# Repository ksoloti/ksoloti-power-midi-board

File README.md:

# Ksoloti Power MIDI addon board

Kicad 6+

Libraries not included, you should be able to retrieve any custom symbols and footprints via the project itself.

3D models not included, always such a hassle with those files, can't be a%$ed.

Gerbers, BOM and CPL (placement) files for JLC included. You should be able to have the board with all SMD parts produced. The remaining (through-hole) parts required are all quite common: 2.54mm headers, DIN-5 MIDI jacks, DC barrel jack...

## Disclaimer: the files are provided as is. I guarantee nothing. Stay safe and double check. If you're not sure if you're doing it right, ask someone with more knowledge for help.

## Schematic
[ksoloti-power-midi-board.pdf](ksoloti-power-midi-board.pdf)

## Rear

## Front

## Bottom

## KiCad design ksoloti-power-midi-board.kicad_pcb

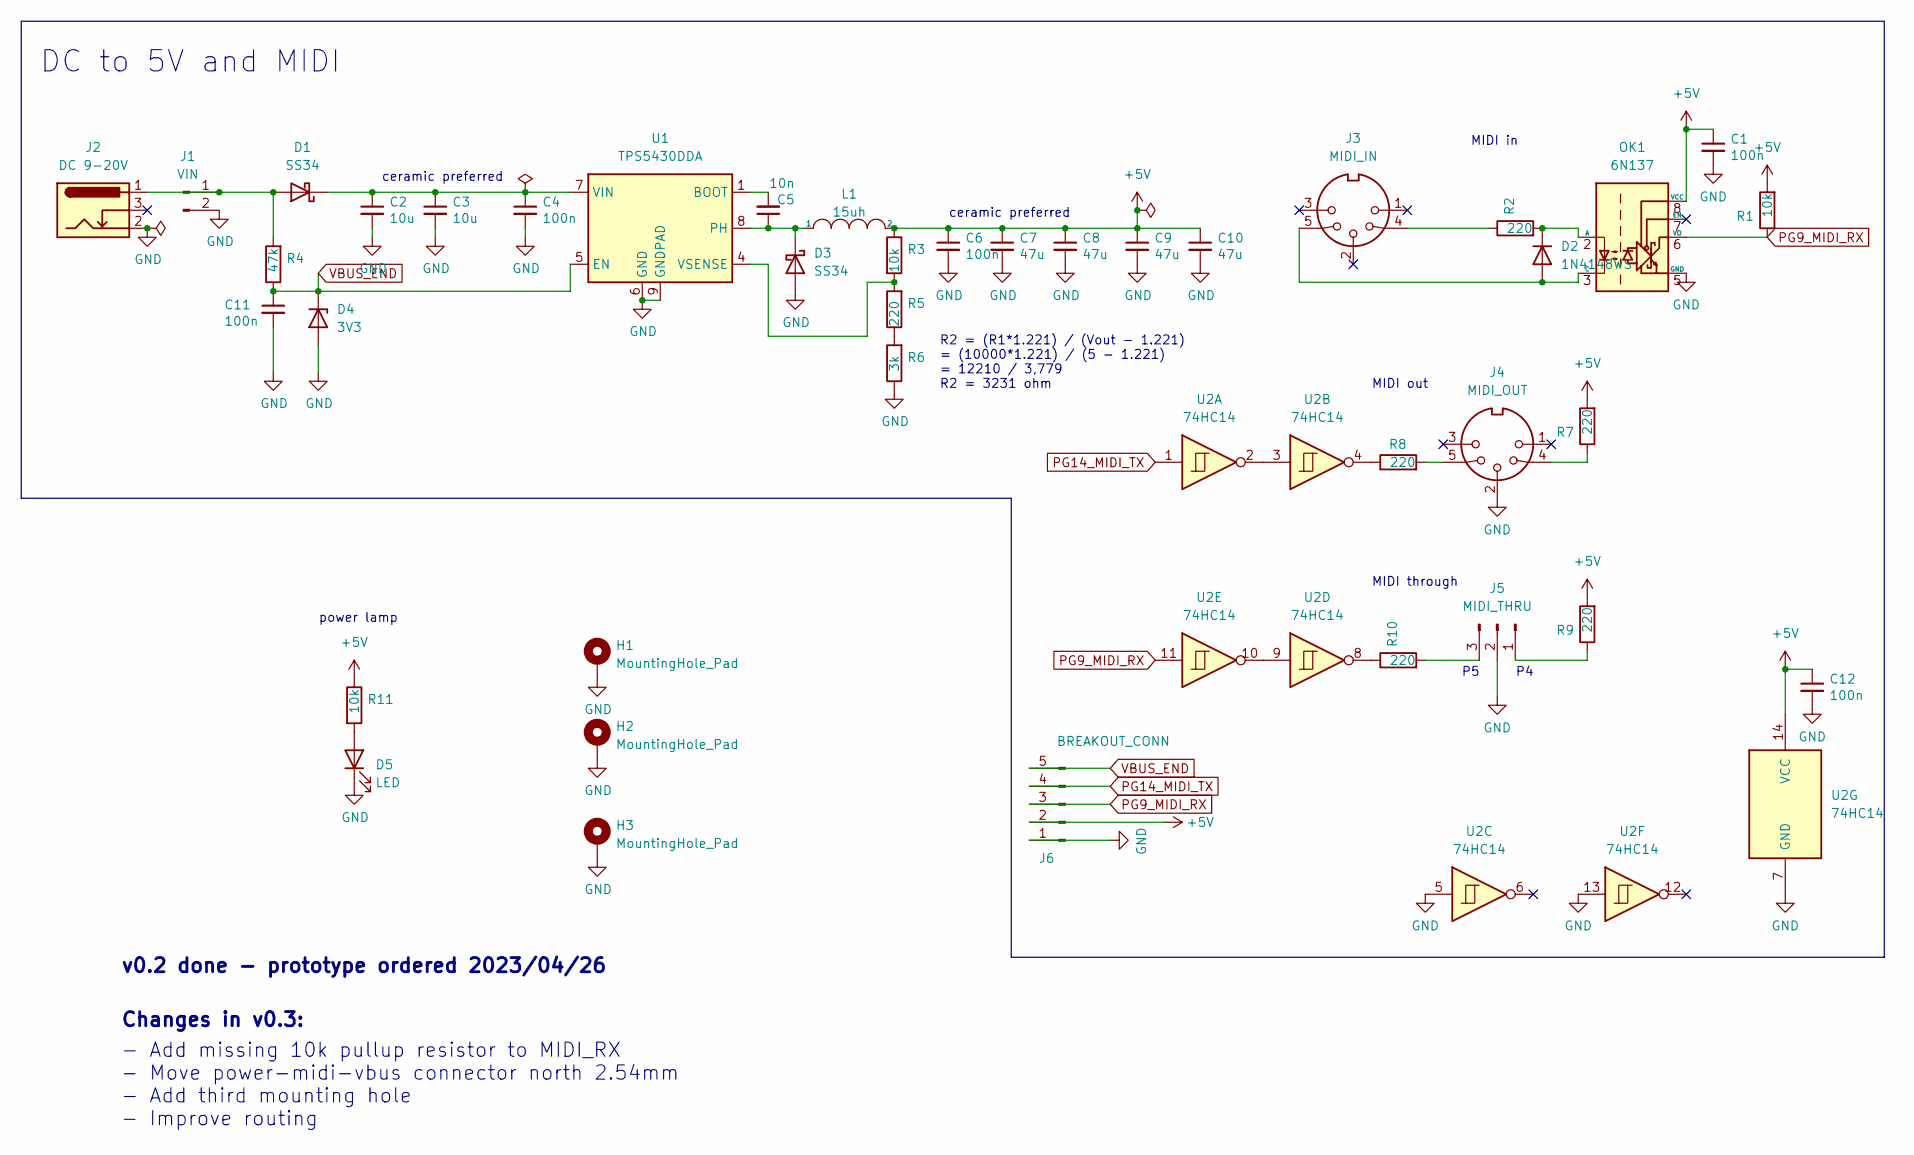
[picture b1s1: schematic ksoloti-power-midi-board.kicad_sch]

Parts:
C1, C4, C6, C11, C12: 100n; C_0603_1608Metric
C2, C3: 10u; C_0603_1608Metric
C5: 10n; C_0603_1608Metric
C7, C8, C9, C10: 47u; C_1206_3216Metric
D1, D3: SS34; D_SMA
D2: 1N4148WS; D_SOD-323
D4: 3V3; D_MiniMELF
D5: LED; LED_0603_1608Metric
H1, H2, H3: MountingHole_Pad; MountingHole_3.2mm_M3_Pad_Via_tight
J1: VIN; PinHeader_1x02_P2.54mm_Vertical
J2: DC 9-20V; dc_socket
J3: MIDI_IN; MIDI_DIN-5_DS-5-01c
J4: MIDI_OUT; MIDI_DIN-5_DS-5-01c
J5: MIDI_THRU; PinHeader_1x03_P2.54mm_Vertical
J6: BREAKOUT_CONN; PinHeader_1x05_P2.54mm_Vertical
L1: 15uh; L_10.4x10.4_H4.8
OK1: 6N137; SMDIP-8_W9.53mm
R1, R3, R11: 10k; R_0603_1608Metric
R2, R5, R7, R8, R9, R10: 220; R_0603_1608Metric
R4: 47k; R_0603_1608Metric
R6: 3k; R_0603_1608Metric
U1: TPS5430DDA; TI_SO-PowerPAD-8_ThermalVias
U2: 74HC14; SOIC-14_3.9x8.7mm_P1.27mm

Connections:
+5V: C1.1, C6.1, C7.1, C8.1, C9.1, C10.1, C12.1, J6.2, L1.2, OK1.8 (VCC), R1.2, R3.1, R7.2, R9.2, R11.1, U2.14 (VCC)
GND: C1.2, C2.2, C3.2, C4.2, C6.2, C7.2, C8.2, C9.2, C10.2, C11.2, C12.2, D3.2 (A), D4.2 (A), D5.1 (K), H1.1, H2.1, H3.1, J1.2, J2.2, J4.2, J5.2, J6.1, OK1.5 (GND), R6.1, U1.6 (GND), U1.9 (GNDPAD), U2.5, U2.7 (GND), U2.13
unnamed: C2.1, C3.1, C4.1, D1.1 (K), U1.7 (VIN)
unnamed: C5.1, D3.1 (K), L1.1, U1.8 (PH)
unnamed: C5.2, U1.1 (BOOT)
unnamed: D1.2 (A), J1.1, J2.1, R4.2
unnamed: D2.1 (K), OK1.2 (A), R2.2
unnamed: D2.2 (A), J3.5, OK1.3 (C)
unnamed: D5.2 (A), R11.2
unnamed: J3.4, R2.1
unnamed: J4.4, R7.1
unnamed: J4.5, R8.2
unnamed: J5.1, R9.1
unnamed: J5.3, R10.2
unnamed: R3.2, R5.2, U1.4 (VSENSE)
unnamed: R5.1, R6.2
unnamed: R8.1, U2.4
unnamed: R10.1, U2.8
unnamed: U2.2, U2.3
unnamed: U2.9, U2.10
PG9_MIDI_RX: J6.3, OK1.6 (VO), R1.1, U2.11
PG14_MIDI_TX: J6.4, U2.1
VBUS_END: C11.1, D4.1 (K), J6.5, R4.1, U1.5 (EN)

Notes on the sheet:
MIDI out
ceramic preferred
power lamp
DC to 5V and MIDI
- Add missing 10k pullup resistor to MIDI_RX - Move power-midi-vbus connector north 2.54mm - Add third mounting hole - Improve routing
MIDI through
v0.2 done - prototype ordered 2023/04/26
MIDI in
Changes in v0.3:
R2 = (R1*1.221) / (Vout - 1.221) = (10000*1.221) / (5 - 1.221) = 12210 / 3,779 R2 = 3231 ohm

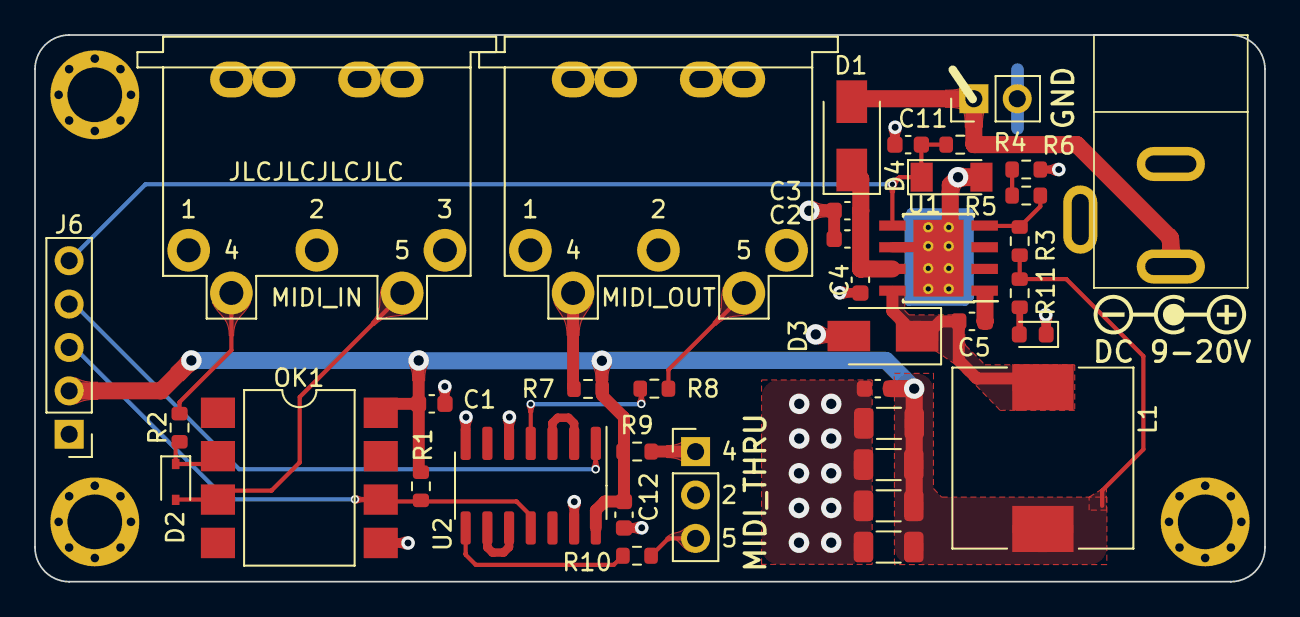
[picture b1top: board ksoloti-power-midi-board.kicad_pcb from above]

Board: 2 copper layers, 72.0 x 32.0 mm, 41 parts (0 on the bottom side), 23 nets.

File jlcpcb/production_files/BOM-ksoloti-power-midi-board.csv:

Comment,Designator,Footprint,LCSC
100n,"C1,C11,C12,C4,C6",C_0603_1608Metric,C14663
6N137,OK1,SMDIP-8_W9.53mm,C16496
1N4148WS,D2,D_SOD-323,C2128
LED,D5,LED_0603_1608Metric,C2286
220,"R10,R2,R5,R7,R8,R9",R_0603_1608Metric,C22962
10k,"R1,R11,R3",R_0603_1608Metric,C25804
47k,R4,R_0603_1608Metric,C25819
15uh,L1,L_10.4x10.4_H4.8,C2847544
3k,R6,R_0603_1608Metric,C4211
74HC14,U2,SOIC-14_3.9x8.7mm_P1.27mm,C5605
10n,C5,C_0603_1608Metric,C57112
3V3,D4,D_MiniMELF,C707189
SS34,"D1,D3",D_SMA,C8678
47u,"C10,C7,C8,C9",C_1206_3216Metric,C96123
10u,"C2,C3",C_0603_1608Metric,C96446
TPS5430DDA,U1,TI_SO-PowerPAD-8_ThermalVias,C9864
MountingHole_Pad,H3,MountingHole_3.2mm_M3_Pad_Via_tight,
VIN,J1,PinHeader_1x02_P2.54mm_Vertical,
MountingHole_Pad,H2,MountingHole_3.2mm_M3_Pad_Via_tight,
MIDI_THRU,J5,PinHeader_1x03_P2.54mm_Vertical,
DC 9-20V,J2,dc_socket,
BREAKOUT_CONN,J6,PinHeader_1x05_P2.54mm_Vertical,
MIDI_IN,J3,MIDI_DIN-5_DS-5-01c,
MountingHole_Pad,H1,MountingHole_3.2mm_M3_Pad_Via_tight,
MIDI_OUT,J4,MIDI_DIN-5_DS-5-01c,

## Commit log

2024-01-03 update gitignore
2024-01-03 add images, readme description
2024-01-03 Kicad gitignore template ignores .csv files, fixed
2024-06-23 add schematic pdf
2024-06-23 include project.db in repo
2024-06-23 edits, update cpl and project.db
2024-06-23 fix link to schematic
